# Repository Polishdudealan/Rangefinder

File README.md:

# Rangefinder
Rangefinder program using FreeRTOS on an STM32F411

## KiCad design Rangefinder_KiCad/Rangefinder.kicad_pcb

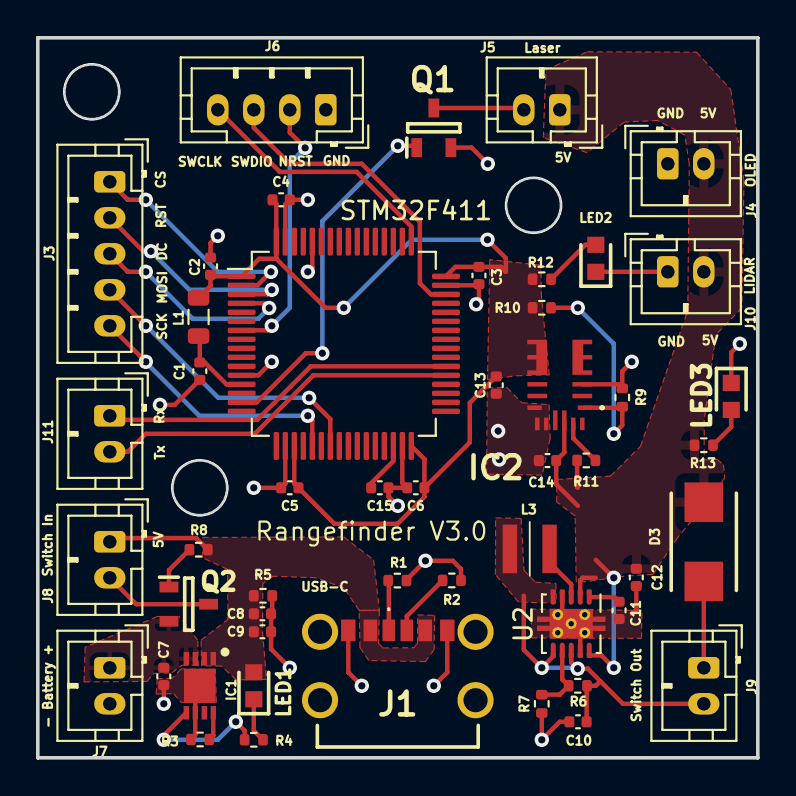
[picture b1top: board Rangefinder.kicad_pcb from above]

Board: 2 copper layers, 40.0 x 40.0 mm, 50 parts (0 on the bottom side), 35 nets.

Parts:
C1, C3, C4, C5, C6, C9: 0.1uF; C_0402_1005Metric
C2, C11, C15: 1uF; C_0402_1005Metric
C7, C8, C14: 10uF; C_0402_1005Metric
C10: 4.7uF; C_0402_1005Metric
C12, C13: 22uF; C_0402_1005Metric
D3: VS-10BQ040HM3_5BT; SMBJ20CDM3I
IC1: Battery_Charger; SON50P300X200X100-9N-D
IC2: 3.3V_Buck; MPM3610AGQVZ
J1: USB-C; USB4125GFA0190
J3: OLED_SPI; JST_PH_B5B-PH-K_1x05_P2.00mm_Vertical
J4: OLED_PWR; JST_PH_B2B-PH-K_1x02_P2.00mm_Vertical
J5: LASER; JST_PH_B2B-PH-K_1x02_P2.00mm_Vertical
J6: DEBUG; JST_PH_B4B-PH-K_1x04_P2.00mm_Vertical
J7: Battery; JST_PH_B2B-PH-K_1x02_P2.00mm_Vertical
J8: Switch_In; JST_PH_B2B-PH-K_1x02_P2.00mm_Vertical
J9: Switch_Out; JST_PH_B2B-PH-K_1x02_P2.00mm_Vertical
J10: LIDAR_PWR; JST_PH_B2B-PH-K_1x02_P2.00mm_Vertical
J11: LIDAR_UART; JST_PH_B2B-PH-K_1x02_P2.00mm_Vertical
L1: 100uH; L_0805_2012Metric
L3: 2.2uH; LQH3NPN100MGRL
LED1: Charging_LED; LEDC1608X90N
LED2: 3.3V_LED; LEDC1608X90N
LED3: 5V_LED; LEDC1608X90N
Q1, Q2: PMV50XPAR; SOT95P230X110-3N
R1, R2: 5.11K; R_0402_1005Metric
R3: 2K; R_0402_1005Metric
R4, R8, R12, R13: 1K; R_0402_1005Metric
R5: 10K; R_0402_1005Metric
R6: 2.2M; R_0402_1005Metric
R7: 200K; R_0402_1005Metric
R9: 24K; R_0402_1005Metric
R10: 75K; R_0402_1005Metric
R11: 100K; R_0402_1005Metric
STM32F411: STM32F411RETx; LQFP-64_10x10mm_P0.5mm
U2: 5V_Boost; Texas_S-PVSON-N10_ThermalVias

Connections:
3.3V_Board: C2.1, C3.2, C4.2, C5.2, C6.2, C13.2, IC2.7 (OUT_1), IC2.8 (OUT_2), IC2.9 (OUT_3), IC2.22 (OUT_4), L1.1, R10.2, R12.2, STM32F411.1 (VBAT), STM32F411.19 (VDD), STM32F411.32 (VDD), STM32F411.48 (VDD), STM32F411.64 (VDD)
5V_Board: C12.1, C14.1, D3.1, IC2.16 (IN), J4.2, J5.1, J10.2, R11.2, R13.2, U2.2 (VOUT), U2.10 (FB)
5V_USB: C8.2, C9.2, IC1.1 (VDD_1), IC1.2 (VDD_2), J1.A9 (VBUS_1), J1.B9 (VBUS_2), J8.1, LED1.2, R5.1, R8.1
/Processor/NRST: J6.2, STM32F411.7 (NRST)
/Processor/OLED_DC: J3.3, STM32F411.4 (PC15)
/Processor/PA1_LASER_SWITCH: Q1.1, STM32F411.15 (PA1)
/Processor/PA5_SPI1_SCK: J3.5, STM32F411.21 (PA5)
/Processor/PA7_SPI1_MOSI: J3.4, STM32F411.23 (PA7)
/Processor/PC6_USART6_TX: J11.2, STM32F411.37 (PC6)
/Processor/PC7_USART6_RX: J11.1, STM32F411.38 (PC7)
/Processor/SPI_CS: J3.1, STM32F411.2 (PC13)
/Processor/SPI_RST: J3.2, STM32F411.3 (PC14)
/Processor/SWCLK: J6.4, STM32F411.49 (PA14)
/Processor/SWDIO: J6.3, STM32F411.46 (PA13)
GND: C1.1, C2.2, C3.1, C4.1, C5.1, C6.1, C7.1, C8.1, C9.1, C10.2, C11.2, C12.2, C13.1, C14.2, C15.2, IC1.6 (VSS), IC1.9 (EP), IC2.3 (AGND), IC2.12 (PGND_1), IC2.13 (PGND_2), IC2.14 (PGND_3), J1.A12 (GND_1), J1.B12 (GND_2), J4.1, J6.1, J7.2, J10.1, LED2.1, LED3.1, Q1.2, R1.2, R2.2, R3.2, R5.2, R7.2, R9.2, STM32F411.12 (VSSA), STM32F411.18 (VSS), STM32F411.31 (VSS), STM32F411.47 (VSS), STM32F411.60 (BOOT0), STM32F411.63 (VSS), U2.4 (PGND), U2.9 (GND), U2.11 (PAD)
unnamed: IC1.8 (PROG), R3.1
unnamed: IC1.5 (STAT), R4.2
unnamed: C7.2, IC1.3 (VBAT_1), IC1.4 (VBAT_2), J7.1, Q2.2
unnamed: IC2.17 (EN), R11.1
unnamed: IC2.1 (FB), R9.1, R10.1
unnamed: J1.A5 (CC1), R1.1
unnamed: J1.B5 (CC2), R2.1
unnamed: J5.2, Q1.3
unnamed: J8.2, Q2.3
unnamed: D3.2, J9.1
unnamed: C10.1, J9.2, L3.1, R6.1, U2.5 (VIN), U2.6 (EN), U2.8 (PS)
unnamed: LED1.1, R4.1
unnamed: LED2.2, R12.1
unnamed: LED3.2, R13.1
unnamed: Q2.1, R8.2
unnamed: C15.1, STM32F411.30 (VCAP1)
unnamed: C1.2, L1.2, STM32F411.13 (VDDA)
unnamed: L3.2, U2.3 (L)
unnamed: R6.2, R7.1, U2.7 (UVLO)
unnamed: C11.1, U2.1 (VAUX)

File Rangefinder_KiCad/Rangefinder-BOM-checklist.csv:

,Source:,D:\Rangefinder\Rangefinder_KiCad\Rangefinder.kicad_sch,,,,,,,,,,,,,
,Date:,9/3/2023 20:40,,,,,,,,,,,,,
,Tool:,Eeschema (7.0.0),,,,,,,,,,,,,
,Generator:,D:\KiCad\7.0\bin\scripting\plugins/bom_csv_grouped_by_value.py,,,,,,,,,,,,,
,Component Count:,47,,,,,,,,,,,,,
,,,,,,,,,,,,,,,
,Collated Components:,,,,,,,,,,,,,,
,,,,,,,,,,,,,,,
,Item,Qty,Reference(s),Value,LibPart,Footprint,Datasheet,DNP,Description,Height,Manufacturer_Name,Manufacturer_Part_Number,Mouser Part Number,Mouser Price/Stock,
8,1,6,"C1, C3, C4, C5, C6, C9",0.1uF,Device:C,Capacitor_SMD:C_0402_1005Metric,~,,,,,,,,
5,2,3,"C2, C11, C15",1uF,Device:C,Capacitor_SMD:C_0402_1005Metric,~,,,,,,,,
5,3,3,"C7, C8, C14",10uF,Device:C,Capacitor_SMD:C_0402_1005Metric,~,,,,,,,,
2,4,1,C10,4.7uF,Device:C,Capacitor_SMD:C_0402_1005Metric,~,,,,,,,,
4,5,2,"C12, C13",22uF,Device:C,Capacitor_SMD:C_0402_1005Metric,~,,,,,,,,
2,6,1,D3,VS-10BQ040HM3_5BT,VS-10BQ040HM3_5BT:VS-10BQ040HM3_5BT,SMBJ20CDM3I,https://www.vishay.com/docs/95723/vs-10bq040hm3.pdf,,,Schottky Diodes & Rectifiers Schottky - SMB-e3,2.44,Vishay,VS-10BQ040HM3/5BT,78-VS-10BQ040HM35BT,https://www.mouser.co.uk/ProductDetail/Vishay-Semiconductors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
3,7,1,IC1,Battery_Charger,MCP73831-2DCI_MC:MCP73831-2DCI_MC,rangefinder_lib:SON50P300X200X100-9N-D,https://www.arrow.com/en/products/mcp73831-2dcimc/microchip-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,,,Linear Battery Charger Controller Li-Ion/Li-Pol 505mA 4.2V 8-Pin DFN EP Tube,1,Microchip,MCP73831-2DCI/MC,579-MCP73831-2DCI/MC,https://www.mouser.co.uk/ProductDetail/Microchip-Technology-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
2,8,1,IC2,3.3V_Buck,MPM3610AGQV-Z:MPM3610AGQV-Z,MPM3610AGQVZ,https://www.monolithicpower.com/pub/media/document/MPM3610A_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,,,,1.65,Monolithic Power Systems (MPS),MPM3610AGQV-Z,946-MPM3610AGQV-Z,https://www.mouser.co.uk/ProductDetail/Monolithic-Power-Syst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
3,9,1,J1,USB-C,USB4125-GF-A-0190:USB4125-GF-A-0190,rangefinder_lib:USB4125GFA0190,,,,USB Connectors USB C Rec GF RA 6P SMT TH Stakes 1.9mm,,GCT (GLOBAL CONNECTOR TECHNOLOGY),USB4125-GF-A-0190,640-USB4125-GF-A-190,https://www.mouser.co.uk/ProductDetail/GCT/USB4125-GF-A-0190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
,10,1,J2,LIDAR,Connector_Generic:Conn_01x04,Connector_PinHeader_2.00mm:PinHeader_1x04_P2.00mm_Vertical,~,,,,,,,,
,11,1,J3,OLED_SPI,Connector_Generic:Conn_01x05,Connector_PinHeader_2.00mm:PinHeader_1x05_P2.00mm_Vertical,~,,,,,,,,
,12,1,J4,OLED_PWR,Connector_Generic:Conn_01x02,Connector_PinHeader_2.00mm:PinHeader_1x02_P2.00mm_Vertical,~,,,,,,,,
,13,1,J5,LASER,Connector_Generic:Conn_01x02,Connector_PinHeader_2.00mm:PinHeader_1x02_P2.00mm_Vertical,~,,,,,,,,
,14,1,J6,DEBUG,Connector_Generic:Conn_01x04,Connector_PinHeader_2.00mm:PinHeader_1x04_P2.00mm_Vertical,~,,,,,,,,
,15,1,J7,Battery,Connector_Generic:Conn_01x02,Connector_PinHeader_2.00mm:PinHeader_1x02_P2.00mm_Vertical,~,,,,,,,,
2,16,1,L1,100uH,Device:L,Inductor_SMD:L_0402_1005Metric,~,,,,,,,,
3,17,1,L3,2.2uH,LQH3NPZ2R2MGRL:LQH3NPZ2R2MGRL,LQH3NPN100MGRL,https://psearch.en.murata.com/inductor/product/LQH3NPZ2R2MGR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,,,LQH3NPZ_GR Series Inductor 2.2uH +/-20% 1212 (3030),1,Murata Electronics,LQH3NPZ2R2MGRL,81-LQH3NPZ2R2MGRL,https://www.mouser.co.uk/ProductDetail/Murata-Electronics/LQ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
4,18,1,LED1,Charging_LED,LTST-C190GKT:LTST-C190GKT,LEDC1608X90N,https://media.digikey.com/pdf/Data%20Sheets/Lite-On%20PDFs/L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,,,Standard LEDs - SMD Green Clear 569nm,0.9,Lite-On,LTST-C190GKT,859-LTST-C190GKT,https://www.mouser.co.uk/ProductDetail/Lite-On/LTST-C190GKT?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
/\,19,1,LED2,5V_LED,LTST-C190GKT:LTST-C190GKT,LEDC1608X90N,https://media.digikey.com/pdf/Data%20Sheets/Lite-On%20PDFs/L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,,,Standard LEDs - SMD Green Clear 569nm,0.9,Lite-On,LTST-C190GKT,859-LTST-C190GKT,https://www.mouser.co.uk/ProductDetail/Lite-On/LTST-C190GKT?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
/\,20,1,LED3,3.3V_LED,LTST-C190GKT:LTST-C190GKT,LEDC1608X90N,https://media.digikey.com/pdf/Data%20Sheets/Lite-On%20PDFs/L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,,,Standard LEDs - SMD Green Clear 569nm,0.9,Lite-On,LTST-C190GKT,859-LTST-C190GKT,https://www.mouser.co.uk/ProductDetail/Lite-On/LTST-C190GKT?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
4,21,2,"Q1, Q2",PMV50XPAR,PMV50XPAR:PMV50XPAR,SOT95P230X110-3N,https://assets.nexperia.com/documents/data-sheet/PMV50XPA.pdf,,,"PMV50XPA - 20 V, P-channel Trench MOSFET@en-us",1.1,Nexperia,PMV50XPAR,771-PMV50XPAR,https://www.mouser.co.uk/ProductDetail/Nexperia/PMV50XPAR?qs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
4,22,2,"R1, R2",5.11K,Device:R,Resistor_SMD:R_0402_1005Metric,~,,,,,,,,
2,23,1,R3,2K,Device:R,Resistor_SMD:R_0402_1005Metric,~,,,,,,,,
6,24,4,"R4, R8, R12, R13",1K,Device:R,Resistor_SMD:R_0402_1005Metric,~,,,,,,,,
2,25,1,R5,10K,Device:R,Resistor_SMD:R_0402_1005Metric,~,,,,,,,,
3,26,1,R6,2.2M,Device:R,Resistor_SMD:R_0402_1005Metric,~,,,,,,,,
3,27,1,R7,200K,Device:R,Resistor_SMD:R_0402_1005Metric,~,Replacing with new one (3) on mouser,,,,,,,
2,28,1,R9,24K,Device:R,Resistor_SMD:R_0402_1005Metric,~,,,,,,,,
2,29,1,R10,75K,Device:R,Resistor_SMD:R_0402_1005Metric,~,,,,,,,,
2,30,1,R11,100K,Device:R,Resistor_SMD:R_0402_1005Metric,~,,,,,,,,
3,31,1,U1,STM32F411RETx,MCU_ST_STM32F4:STM32F411RETx,Package_QFP:LQFP-64_10x10mm_P0.5mm,https://www.st.com/resource/en/datasheet/stm32f411re.pdf,,,,,,,,
1,32,1,U2,5V_Boost,Regulator_Switching:TPS61200DRC,Package_SON:Texas_S-PVSON-N10_ThermalVias,http://www.ti.com/lit/ds/symlink/tps61200.pdf,,,,,,,,

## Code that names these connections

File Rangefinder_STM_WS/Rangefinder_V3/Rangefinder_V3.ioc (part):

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Mcu.Name=STM32F411R(C-E)Tx
Mcu.Package=LQFP64
Mcu.UserName=STM32F411RETx
PA1.Signal=S_TIM2_CH2
PA13.Mode=Serial_Wire
PA13.Signal=SYS_JTMS-SWDIO
PA14.Mode=Serial_Wire
PA14.Signal=SYS_JTCK-SWCLK
PA5.Mode=TX_Only_Simplex_Unidirect_Master
PA5.Signal=SPI1_SCK
PA7.Mode=TX_Only_Simplex_Unidirect_Master
PA7.Signal=SPI1_MOSI
PC11.GPIOParameters=GPIO_Label
PC11.GPIO_Label=Task 1
PC11.Signal=GPIO_Output
PC13-ANTI_TAMP.GPIOParameters=GPIO_PuPd,GPIO_Label
PC13-ANTI_TAMP.GPIO_Label=SPI_CS
PC13-ANTI_TAMP.GPIO_PuPd=GPIO_NOPULL
PC13-ANTI_TAMP.Signal=GPIO_Output
PC14-OSC32_IN.GPIOParameters=GPIO_PuPd,GPIO_Label,GPIO_ModeDefaultOutputPP
PC14-OSC32_IN.GPIO_Label=SPI_RST
PC14-OSC32_IN.GPIO_ModeDefaultOutputPP=GPIO_MODE_OUTPUT_PP
PC14-OSC32_IN.GPIO_PuPd=GPIO_NOPULL
PC14-OSC32_IN.Signal=GPIO_Output
PC15-OSC32_OUT.GPIOParameters=GPIO_PuPd,GPIO_Label,GPIO_ModeDefaultOutputPP
PC15-OSC32_OUT.GPIO_Label=OLED_DC
PC15-OSC32_OUT.GPIO_ModeDefaultOutputPP=GPIO_MODE_OUTPUT_PP
PC15-OSC32_OUT.GPIO_PuPd=GPIO_NOPULL
PC15-OSC32_OUT.Signal=GPIO_Output
PC2.GPIOParameters=GPIO_Label
PC2.GPIO_Label=OLED_DC_new
PC2.Signal=GPIO_Output
PC3.GPIOParameters=GPIO_Label
PC3.GPIO_Label=OLED_RST_new
PC3.Signal=GPIO_Output
PC6.Mode=Asynchronous
PC6.Signal=USART6_TX
PC7.Mode=Asynchronous
PC7.Signal=USART6_RX
PD2.GPIOParameters=GPIO_Label
PD2.GPIO_Label=Task 2
PD2.Signal=GPIO_Output
RCC.HSE_VALUE=25000000
RCC.SYSCLKFreq_VALUE=64000000
RCC.SYSCLKSource=RCC_SYSCLKSOURCE_PLLCLK
board=custom

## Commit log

2024-03-20 Working version
